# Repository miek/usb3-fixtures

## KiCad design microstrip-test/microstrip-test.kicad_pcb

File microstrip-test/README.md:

# Microstrip test

This is a board to test microstrip & connector launch dimensions for JLCPCB's 7628 stackup. It uses the Rosenberger 32K243-40ML5 edge-launch SMA connector.

The even-numbered connectors use Rosenberger's suggested footprint as-is, and the odd-numbered connectors resize the signal trace to match the microstrip.
It has traces designed for 45, 50, and 55 ohms based on JLCPCB's calculator and includes a fourth trace that matches the Rosenberger footprint

## Results

### Test setup

The 50 ohm trace was populated and tested using an Agilent 86100A & 54754A TDR module connected to J4, with a 50 ohm load connected to J3.

The TDR response is shown below. The first blue waveform was captured with J4 disconnected, and the second blue waveform was captured with J4 connected and J3 disconnected - this helps to visualise where the DUT lies in time.
The response shows a drop in impedance at the J4 footprint, due to the wider trace in the suggested footprint. After that the microstrip is nominally 50 ohm with some variation, likely due to the fiber weave. The adjusted trace width on the J3 footprint seems to be a good match and maintains ~50 ohms through to the load.

Adding some markers shows that the microstrip varies between ~51.1 and 52.7 ohms. It may be possible to tune for a better match but it will depend on the range of manufacturing variation.

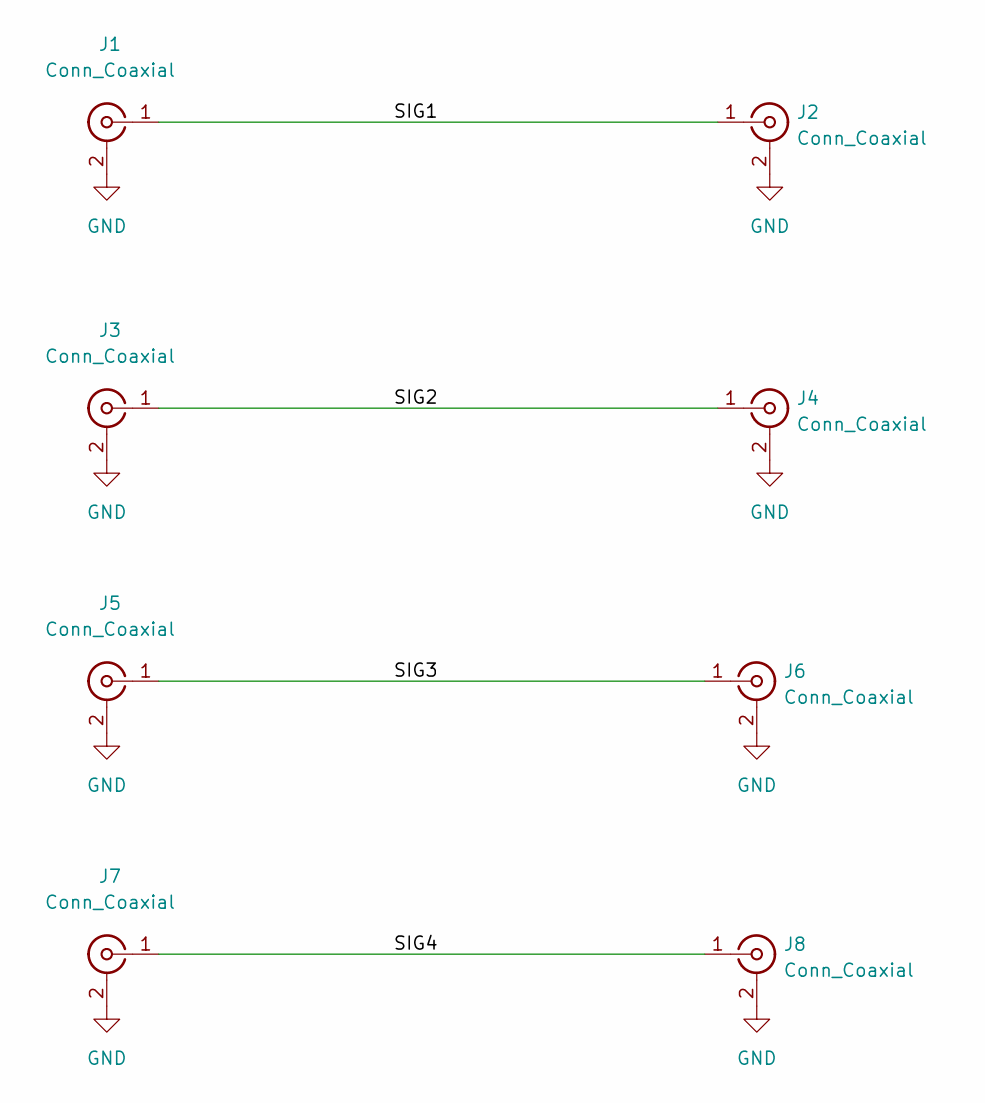
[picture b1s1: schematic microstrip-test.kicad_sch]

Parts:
J1, J2, J3, J4, J5, J6, J7, J8: Conn_Coaxial; CONN_SMA_EDGE_ROSENBERGER_32K243_40ML5

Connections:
/SIG1: J1.1 (In), J2.1 (In)
/SIG2: J3.1 (In), J4.1 (In)
/SIG3: J5.1 (In), J6.1 (In)
/SIG4: J7.1 (In), J8.1 (In)
GND: J1.2 (Ext), J2.2 (Ext), J3.2 (Ext), J4.2 (Ext), J5.2 (Ext), J6.2 (Ext), J7.2 (Ext), J8.2 (Ext)

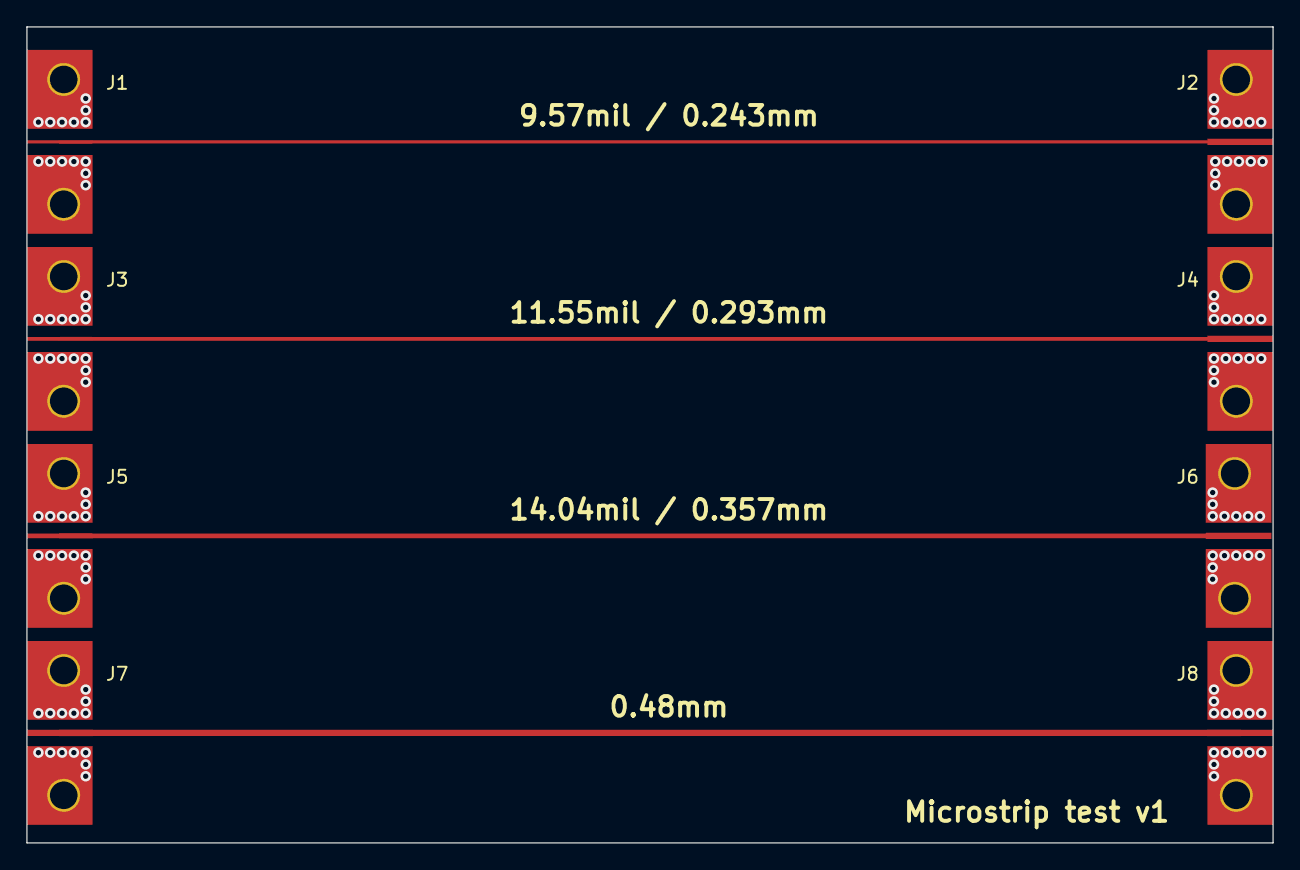
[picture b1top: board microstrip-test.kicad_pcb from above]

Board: 4 copper layers, 94.9 x 62.1 mm, 8 parts (0 on the bottom side), 5 nets.

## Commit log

2022-09-05 Add microstrip test board
2022-09-05 Add microstrip-test-v1 test results
